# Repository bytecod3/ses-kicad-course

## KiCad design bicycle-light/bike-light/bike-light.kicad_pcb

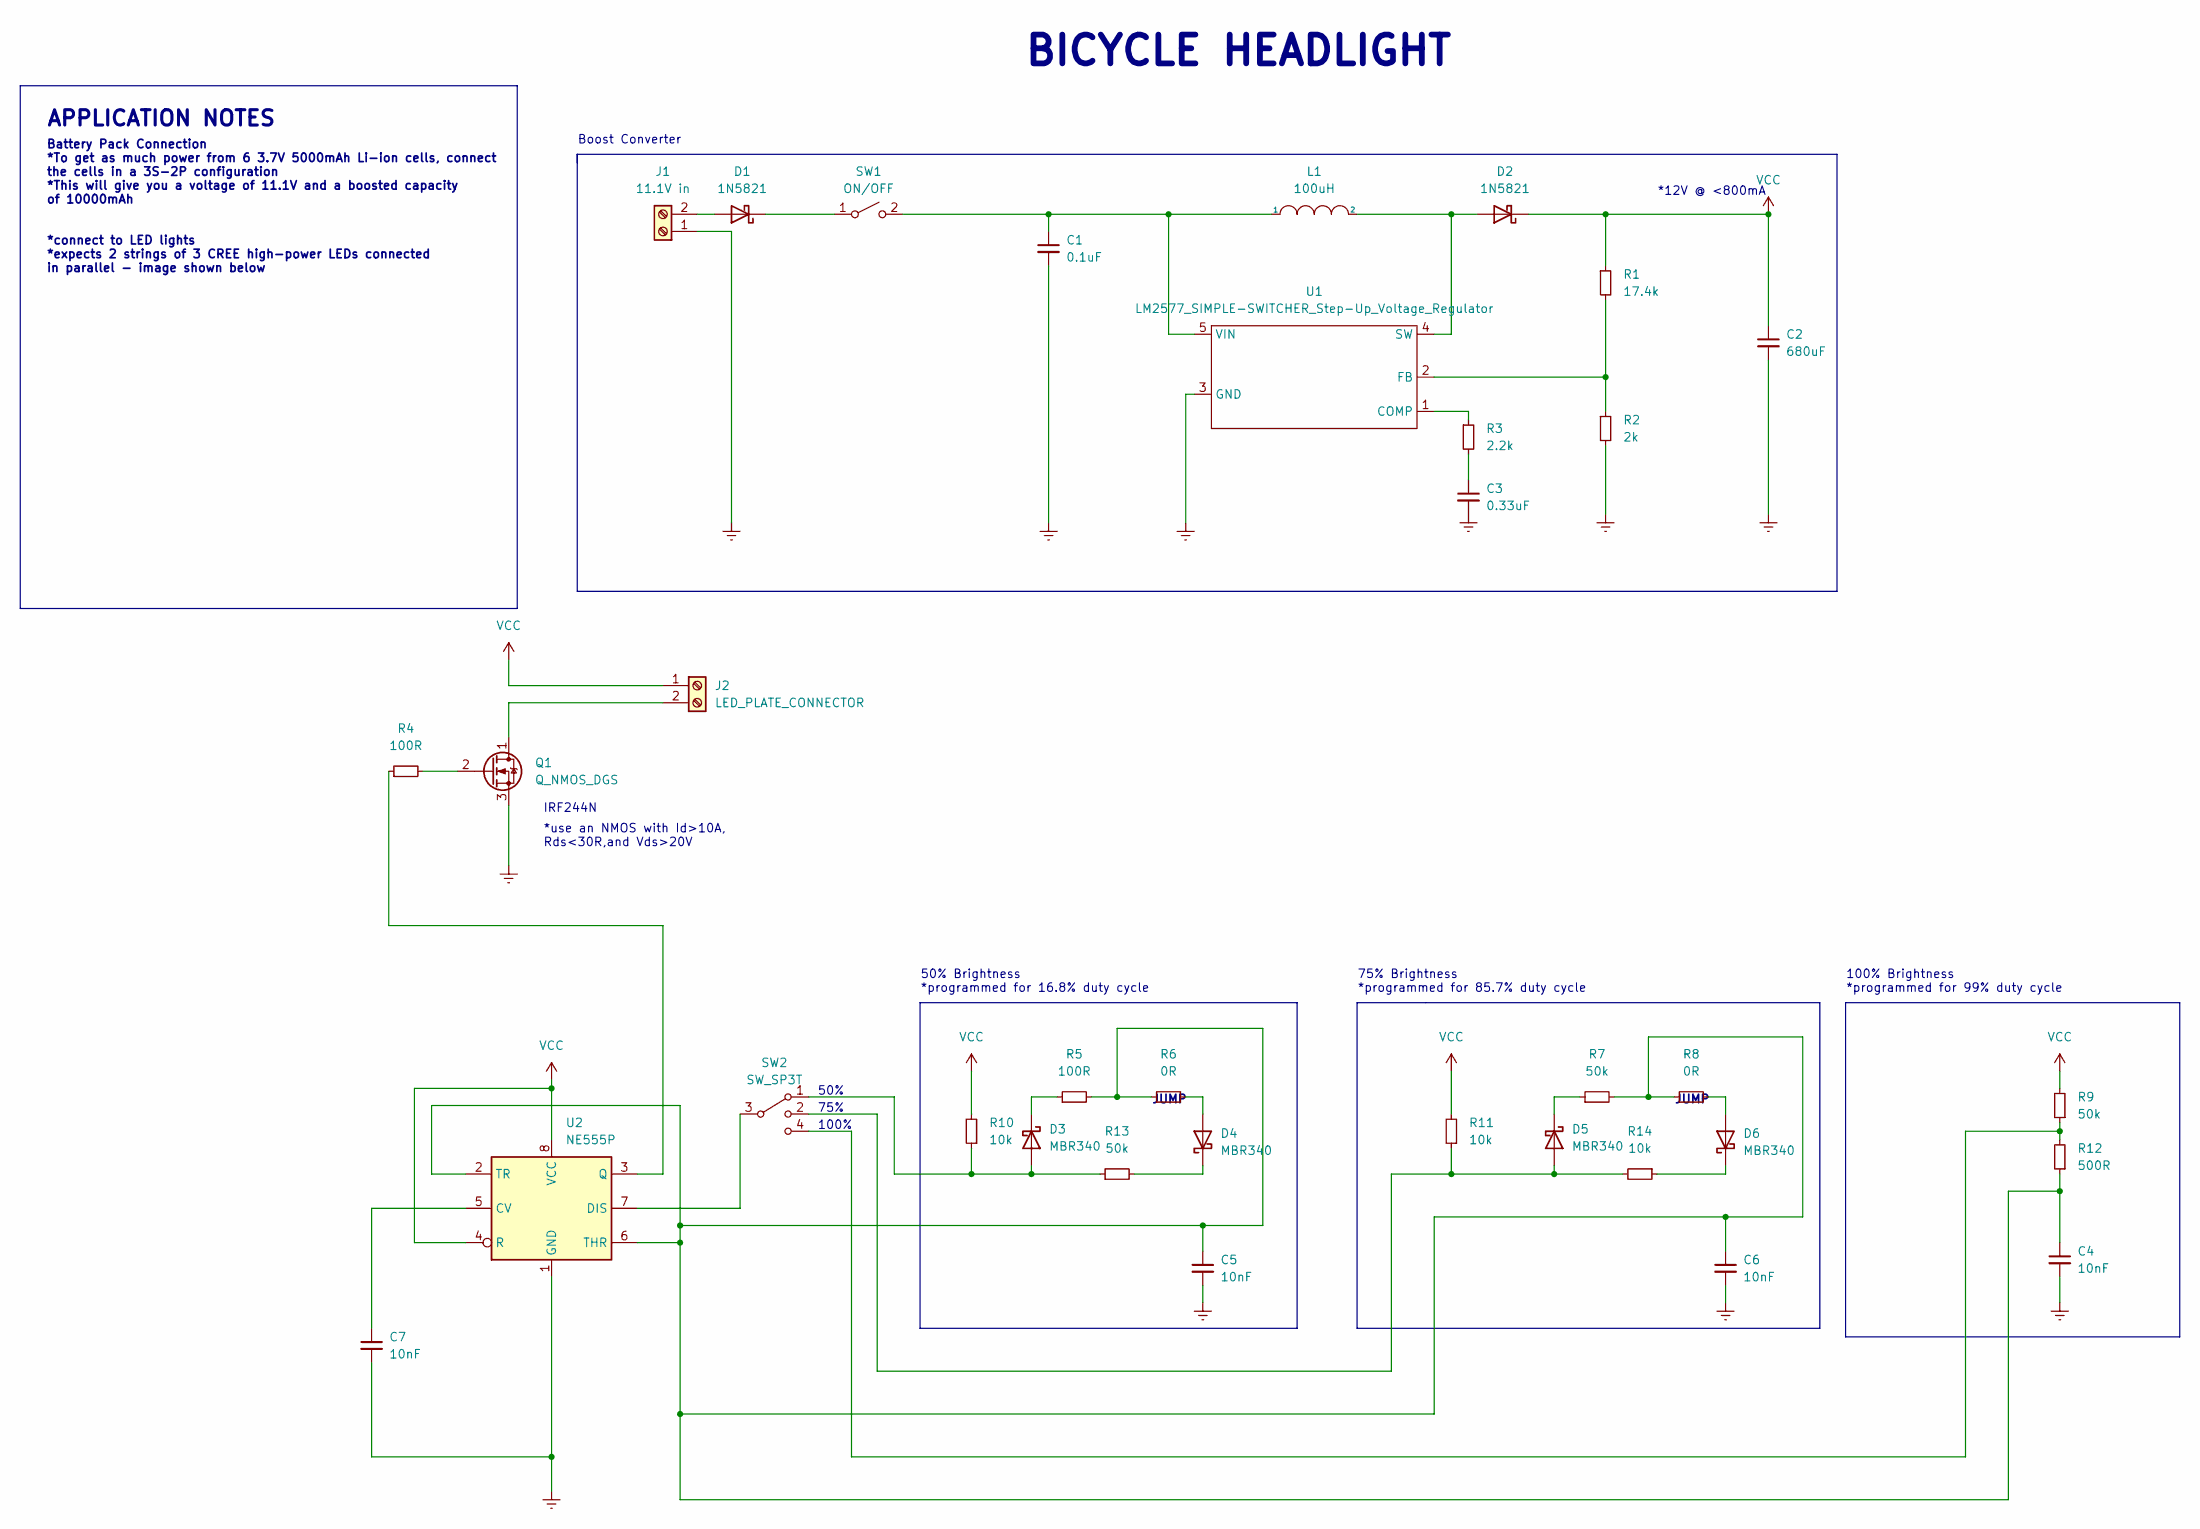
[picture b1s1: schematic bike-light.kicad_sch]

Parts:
C1: 0.1uF; CP_Elec_4x5.4; JLCPart# C271438
C2: 680uF; CP_Elec_10x10.5; DigikeyPart# P14514-ND
C3: 0.33uF; CP_Elec_4x5.4; JLCPart# C271437
C4, C5, C6, C7: 10nF; C_0805_2012Metric; JLCPart# C105947
D1, D2: 1N5821; D_DO-201AD_P15.24mm_Horizontal; DigikeyPart# 1801-1N5821TR-ND
D3, D4, D5, D6: MBR340; D_DO-201AD_P15.24mm_Horizontal; DigikeyPart# 1801-1N5821TR-ND
J1: 11.1V in; JST_EH_S2B-EH_1x02_P2.50mm_Horizontal; Part# 1-1123723-2
J2: LED_PLATE_CONNECTOR; JST_EH_S2B-EH_1x02_P2.50mm_Horizontal; Part# 1-1123723-2
L1: 100uH; L_Bourns_SRR1208_12.7x12.7mm; DigikeyPart# 118-SRR1206-101YLCT-ND
Q1: Q_NMOS_DGS; SOT-23; DigikeyPart# DMN65D8L-7DICT-ND
R1: 17.4k; R_0805_2012Metric_Pad1.20x1.40mm_HandSolder; DigikeyPart# RMCF0805FT17K4CT-ND
R2: 2k; R_0805_2012Metric_Pad1.20x1.40mm_HandSolder; DigikeyPart# RG20P2.0KBCT-ND
R3: 2.2k; R_0805_2012Metric_Pad1.20x1.40mm_HandSolder; DigikeyPart# P2.2KDACT-ND
R4: 100R; R_0805_2012Metric_Pad1.20x1.40mm_HandSolder
R5: 100R; R_0805_2012Metric_Pad1.20x1.40mm_HandSolder; JLCPart# 541-100TCT-ND
R6, R8: 0R; SolderJumper-2_P1.3mm_Bridged2Bar_Pad1.0x1.5mm
R7, R9, R13: 50k; R_0805_2012Metric_Pad1.20x1.40mm_HandSolder; DigikeyPart# PLT0805-50KACT-ND
R10, R11, R14: 10k; R_0805_2012Metric_Pad1.20x1.40mm_HandSolder; JLCPart# C510098
R12: 500R; R_0805_2012Metric_Pad1.20x1.40mm_HandSolder; DigikeyPart# Y1629-500ACT-ND
SW1: ON/OFF; SW_CuK_JS202011AQN_DPDT_Angled; DigikeyPart# 401-2000-ND
SW2: SW_SP3T; SW_CuK_JS202011AQN_DPDT_Angled; DigikeyPart# 401-2000-ND
U1: LM2577_SIMPLE-SWITCHER_Step-Up_Voltage_Regulator; TO-263-5_TabPin3; JLCPart# C17117
U2: NE555P; SOIC-8_3.9x4.9mm_P1.27mm; DigikeyPart# 296-6501-1-ND

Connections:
Earth: C1.2, C2.2, C3.2, C4.2, C5.2, C6.2, C7.2, J1.1, Q1.3 (S), R2.2, U1.3 (GND), U2.1 (GND)
unnamed: C1.1, L1.1, SW1.2 (B), U1.5 (VIN)
unnamed: C3.1, R3.2
unnamed: C7.1, U2.5 (CV)
unnamed: D1.1 (K), SW1.1 (A)
unnamed: D1.2 (A), J1.2
unnamed: D2.2 (A), L1.2, U1.4 (SW)
unnamed: D3.1 (K), R5.1
unnamed: D3.2 (A), R10.1, R13.1, SW2.1
unnamed: D4.1 (K), R13.2
unnamed: D4.2 (A), R6.2
unnamed: D5.1 (K), R7.1
unnamed: D5.2 (A), R11.1, R14.2, SW2.2
unnamed: D6.1 (K), R14.1
unnamed: D6.2 (A), R8.2
unnamed: J2.2, Q1.1 (D)
unnamed: Q1.2 (G), R4.2
unnamed: R1.2, R2.1, U1.2 (FB)
unnamed: R3.1, U1.1 (COMP)
unnamed: R4.1, U2.3 (Q)
unnamed: C4.1, C5.1, C6.1, R5.2, R6.1, R7.2, R8.1, R12.1, U2.2 (TR), U2.6 (THR)
unnamed: R9.1, R12.2, SW2.4
unnamed: SW2.3, U2.7 (DIS)
VCC: C2.1, D2.1 (K), J2.1, R1.1, R9.2, R10.2, R11.2, U2.4 (R), U2.8 (VCC)

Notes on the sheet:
75% Brightness *programmed for 85.7% duty cycle
Battery Pack Connection *To get as much power from 6 3.7V 5000mAh Li-ion cells, connect the cells in a 3S-2P configuration *This will give you a voltage of 11.1V and a boosted capacity of 10000mAh
*connect to LED lights *expects 2 strings of 3 CREE high-power LEDs connected in parallel - image shown below
Boost Converter
*12V @ <800mA
APPLICATION NOTES
100% Brightness *programmed for 99% duty cycle
BICYCLE HEADLIGHT
IRF244N
75%
*use an NMOS with Id>10A, Rds<30R,and Vds>20V
JUMP
50% Brightness *programmed for 16.8% duty cycle
100%
50%

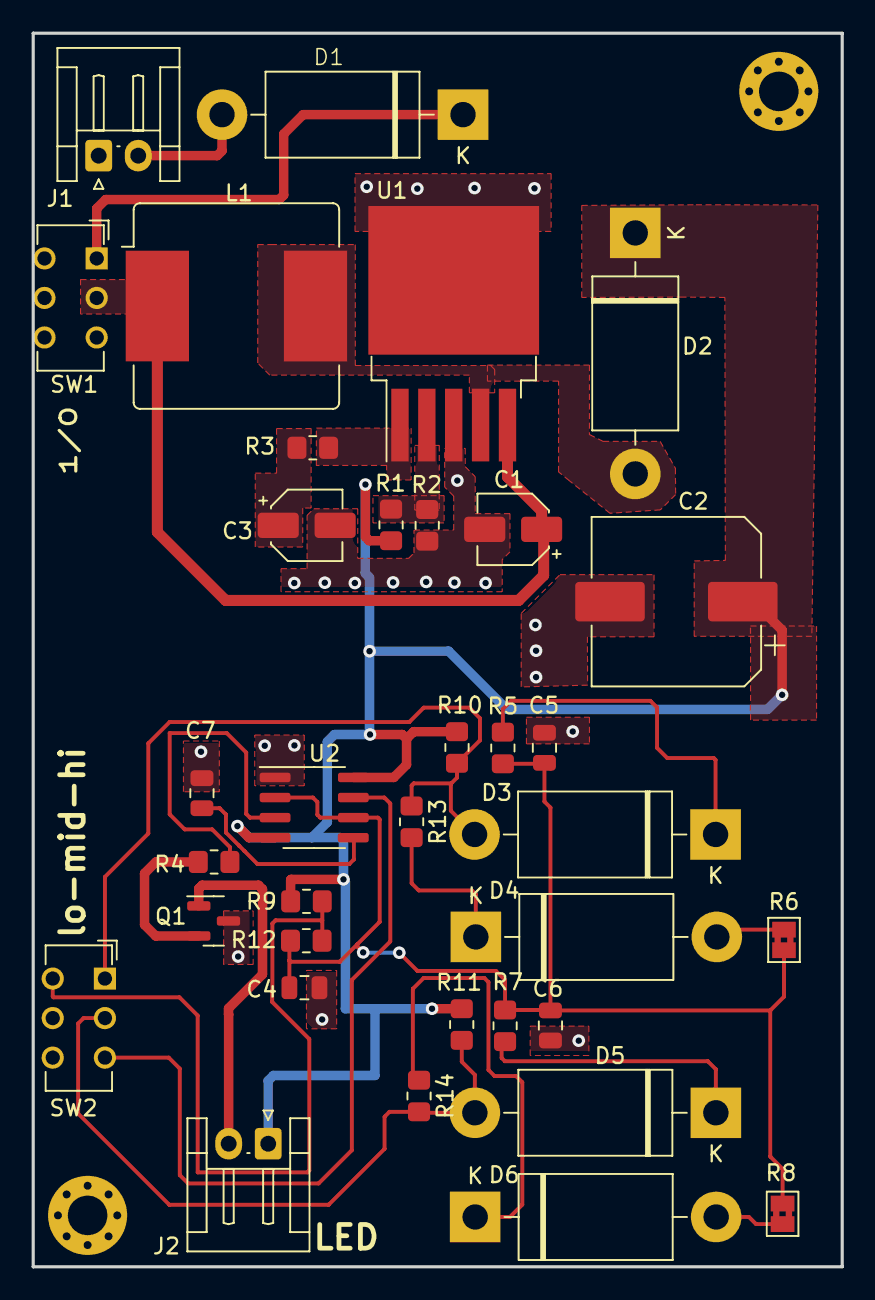
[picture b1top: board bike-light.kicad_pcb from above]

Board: 2 copper layers, 51.2 x 78.0 mm, 35 parts (0 on the bottom side), 24 nets.

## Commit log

2023-10-12 added notes
